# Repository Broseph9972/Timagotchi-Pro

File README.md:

# Timagotchi-Pro
The Timagotchi-Pro is a remake of my magnum opus project, the Timagotchi. for info on that checkout [The original Site](https://timagotchi.dev). this is meant to make it accessible for more than just "School schedules" and moving the price from around $50 without crazy deals to ~~$20.~~ ~~$40~~ ~32[^1] I wanted to make it cooler with a joystick, but i kept the budget as small as possible. kinda wish i didnt tbh.
[^1]:(it will be much cheaper if i ever make multiple, but shipping and using premade devboards and screens make it much more annoying The Timagotchi *(time-a-got-chee)* is a low-cost device that helps with adhd time blindness[^2]
[^2]:You're bad at telling how much time has passed
with a progress bar and other features shown to help people with time blindness at a quick glance with many other useful features.
---

<p align="center">
  
  &nbsp;
  
</p>

# Assembly

To assemble it it simply Solder the buttons, capacitors, screen connector, xiao, speaker, and JST for battery on, then use the FPC cable from the screen, bend it in a "Z" so it fits in the connectors the right way and also plug in the battery it should automatically charge via usb-c. once the pcb is done, There are 2 parts to the cad, a top and bottom half. Insert the pcb, connect the screen afterputting it in the indent on top. put them together with glue, or don't they should still stay together. you may have to seperate the 2 parts in your slicer, but it should work be easily printable.

# Usage
To use it, simply interact with the menu using the buttons like a d-pad. It's very intuitive, im sure you'll understand.

# Why?
I made it becuase i personally have issues telling how much time is left in class, and was really really bored. turned out to be a really really good idea. ive sold these at school to other kids with adhd and actually made profit??? i made the v2 to reduce price and DRASTICALLY improve quality
---
Some upgrades over the earlier version include

- Price reduction
- Speaker
- Nicer buttons
- kinda better case
- No reliance on raspberry pi
- **A Battery**
- Touchscreen

| Quantity | Name                   | Price  | Link                                                                                                                                                                                                                                                                                                                                                                                                                                                                                                                                                                                                                                                            |
| -------- | ---------------------- | ------ | --------------------------------------------------------------------------------------------------------------------------------------------------------------------------------------------------------------------------------------------------------------------------------------------------------------------------------------------------------------------------------------------------------------------------------------------------------------------------------------------------------------------------------------------------------------------------------------------------------------------------------------------------------------- |
| 1        | Conn_01x02_Pin         | $0.11  | https://www.digikey.com/en/products/detail/jst-sales-america-inc/B2B-PH-K-S/926611                                                                                                                                                                                                                                                                                                                                                                                                                                                                                                                                                                              |
| 1        | Speaker                | $4.24  | https://www.digikey.com/en/products/detail/same-sky-formerly-cui-devices/CMS-201438-058S/22602291                                                                                                                                                                                                                                                                                                                                                                                                                                                                                                                                                               |
| 1        | CMS-201438-058S        | $1.60  | https://www.digikey.com/en/products/detail/molex/2005280180/13538830\                                                                                                                                                                                                                                                                                                                                                                                                                                                                                                                                                                                           |
| 1        | XIAO-ESP32-S3-Plus-SMD | $1.86  | Esp32-s3                                                                                                                                                                                                                                                                                                                                                                                                                                                                                                                                                                                                                                                        |
| 1        | MAX98357A              | $6.02  | https://www.aliexpress.us/item/3256807631636428.html?algo_exp_id=60dd1b32-b01c-4ea4-aa7c-080ad8d2e19e-10&pdp_ext_f=%7B%22order%22%3A%2246%22%2C%22eval%22%3A%221%22%2C%22fromPage%22%3A%22search%22%7D&utparam-url=scene%3Asearch%7Cquery_from%3A%7Cx_object_id%3A1005007817951180%7C_p_origin_prod%3A                                                                                                                                                                                                                                                                                                                                                          |
| 1        | PCB                    | $5.22  | JLCPCB                                                                                                                                                                                                                                                                                                                                                                                                                                                                                                                                                                                                                                                          |
| 1        | Battery                | $0.99  | https://www.aliexpress.us/item/3256802733222186.html?spm=a2g0o.productlist.main.2.573662c3rEHzeH&algo_pvid=776a5850-4451-4f10-b9ac-21b38e442e2a&algo_exp_id=776a5850-4451-4f10-b9ac-21b38e442e2a-1&pdp_ext_f=%7B%22order%22%3A%221283%22%2C%22eval%22%3A%221%22%2C%22fromPage%22%3A%22search%22%7D&pdp_npi=6%40dis%21USD%2112.94%210.99%21%21%2112.94%210.99%21%402101d49617782838741088519ed7e7%2112000028368881594%21sea%21US%210%21ABX%211%210%21n_tag%3A-29910%3Bd%3A88f1f0e6%3Bm03_new_user%3A-29895%3BpisId%3A5000000203520967&curPageLogUid=4m6JpZeIsJ89&utparam-url=scene%3Asearch%7Cquery_from%3A%7Cx_object_id%3A1005002919536938%7C_p_origin_prod%3A |
| 1        | Screen                 | $11.99 | https://www.waveshare.com/product/displays/lcd-oled/lcd-oled-3/1.47inch-touch-lcd.htm                                                                                                                                                                                                                                                                                                                                                                                                                                                                                                                                                                           |
|          | Total                  | $32.03 |                                                                                                                                                                                                                                                                                                                                                                                                                                                                                                                                                                                                                                                                 |

This is a project for Hack Club Fallout.

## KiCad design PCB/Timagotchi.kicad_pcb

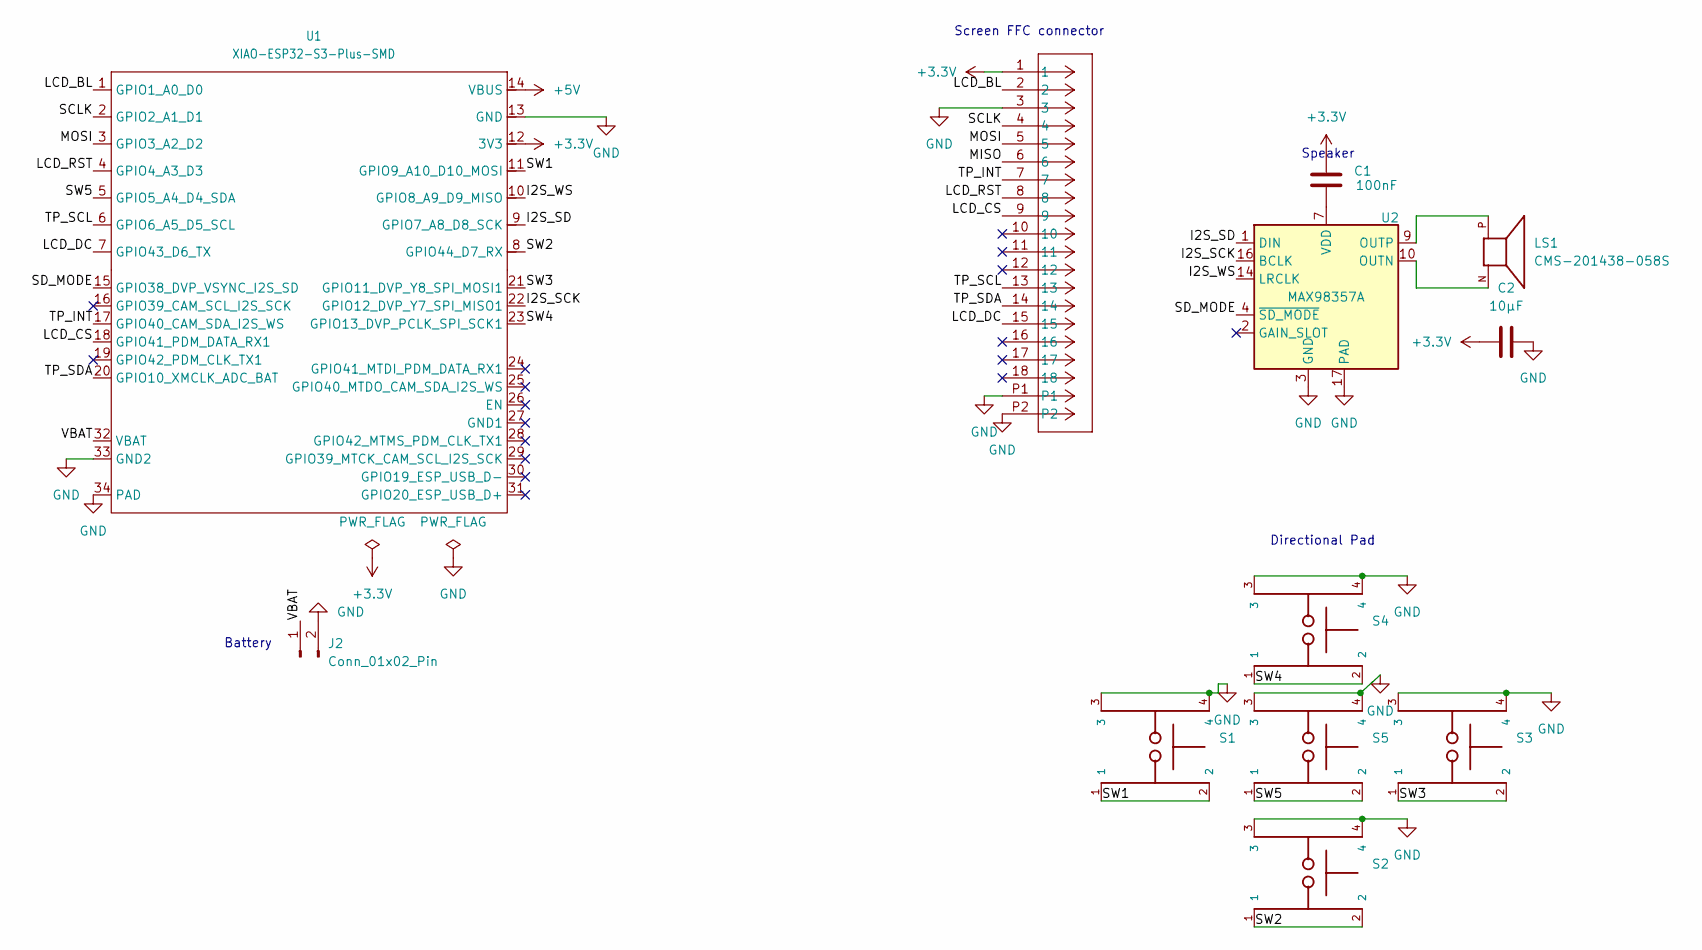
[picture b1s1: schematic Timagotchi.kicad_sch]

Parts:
C1: 100nF; C_0805_2012Metric_Pad1.18x1.45mm_HandSolder
C2: 10µF; C_0805_2012Metric_Pad1.18x1.45mm_HandSolder
J2: Conn_01x02_Pin; JST_PH_B2B-PH-K_1x02_P2.00mm_Vertical
LS1: CMS-201438-058S; SPKR_CMS-201438-058S; PARTREV 1.03
S1, S2, S3, S4, S5: TL3342F160QG; SW_TL3342F160QG
ScreenConnector1: 2005280180; CON_2005280180_MOL
U1: XIAO-ESP32-S3-Plus-SMD
U2: MAX98357A; TQFN-16-1EP_3x3mm_P0.5mm_EP1.23x1.23mm

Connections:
+3.3V: C1.1, C2.1, ScreenConnector1.1, U1.12 (3V3)
+5V: U1.14 (VBUS)
/I2S_SCK: U1.22 (GPIO12_DVP_Y7_SPI_MISO1), U2.16 (BCLK)
/I2S_SD: U1.9 (GPIO7_A8_D8_SCK), U2.1 (DIN)
/I2S_WS: U1.10 (GPIO8_A9_D9_MISO), U2.14 (LRCLK)
/LCD_BL: ScreenConnector1.2, U1.1 (GPIO1_A0_D0)
/LCD_CS: ScreenConnector1.9, U1.18 (GPIO41_PDM_DATA_RX1)
/LCD_DC: ScreenConnector1.15, U1.7 (GPIO43_D6_TX)
/LCD_RST: ScreenConnector1.8, U1.4 (GPIO4_A3_D3)
/MISO: ScreenConnector1.6
/MOSI: ScreenConnector1.5, U1.3 (GPIO3_A2_D2)
/SCLK: ScreenConnector1.4, U1.2 (GPIO2_A1_D1)
/SD_MODE: U1.15 (GPIO38_DVP_VSYNC_I2S_SD), U2.4 (~SD_MODE)
/SW1: S1.1, S1.2, U1.11 (GPIO9_A10_D10_MOSI)
/SW2: S2.1, S2.2, U1.8 (GPIO44_D7_RX)
/SW3: S3.1, S3.2, U1.21 (GPIO11_DVP_Y8_SPI_MOSI1)
/SW4: S4.1, S4.2, U1.23 (GPIO13_DVP_PCLK_SPI_SCK1)
/SW5: S5.1, S5.2, U1.5 (GPIO5_A4_D4_SDA)
/TP_INT: ScreenConnector1.7, U1.17 (GPIO40_CAM_SDA_I2S_WS)
/TP_SCL: ScreenConnector1.13, U1.6 (GPIO6_A5_D5_SCL)
/TP_SDA: ScreenConnector1.14, U1.20 (GPIO10_XMCLK_ADC_BAT)
/VBAT: J2.1, U1.32 (VBAT)
GND: C2.2, J2.2, S1.3, S1.4, S2.3, S2.4, S3.3, S3.4, S4.3, S4.4, S5.3, S5.4, ScreenConnector1.3, ScreenConnector1.P1, ScreenConnector1.P2, U1.13 (GND), U1.33 (GND2), U1.34 (PAD), U2.3 (GND), U2.11 (GND), U2.15 (GND), U2.17 (PAD)
unnamed: C1.2, U2.7 (VDD), U2.8 (VDD)
unnamed: LS1.N, U2.10 (OUTN)
unnamed: LS1.P, U2.9 (OUTP)

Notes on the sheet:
Directional Pad
Battery
Speaker
Screen FFC connector

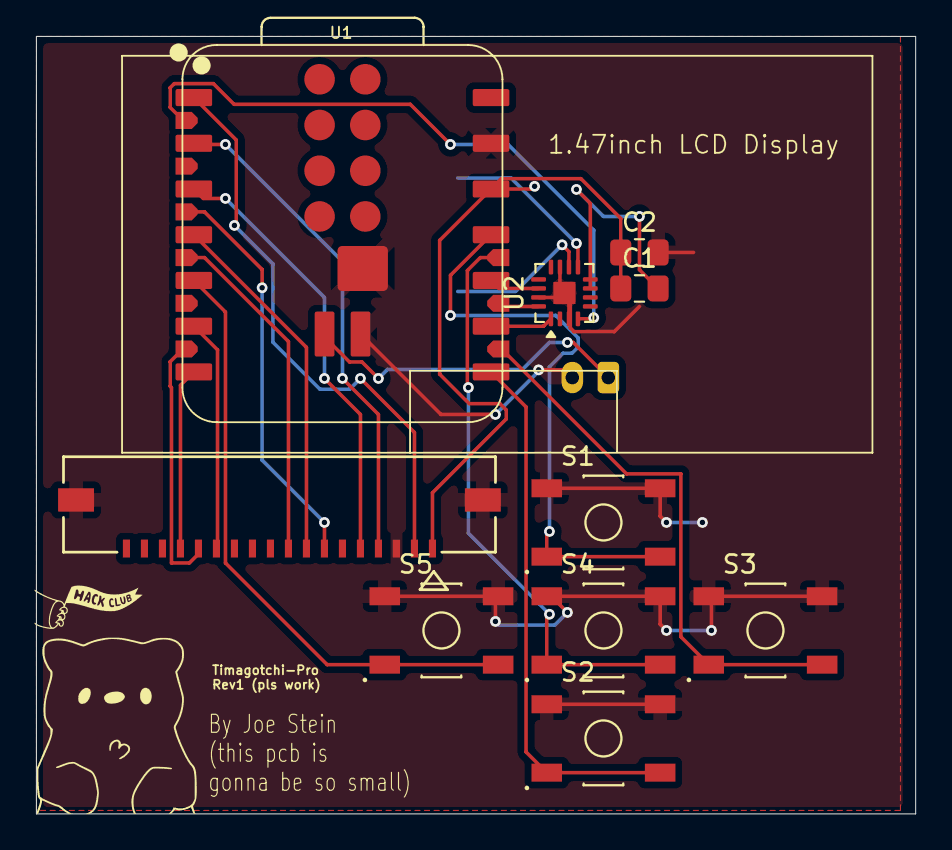
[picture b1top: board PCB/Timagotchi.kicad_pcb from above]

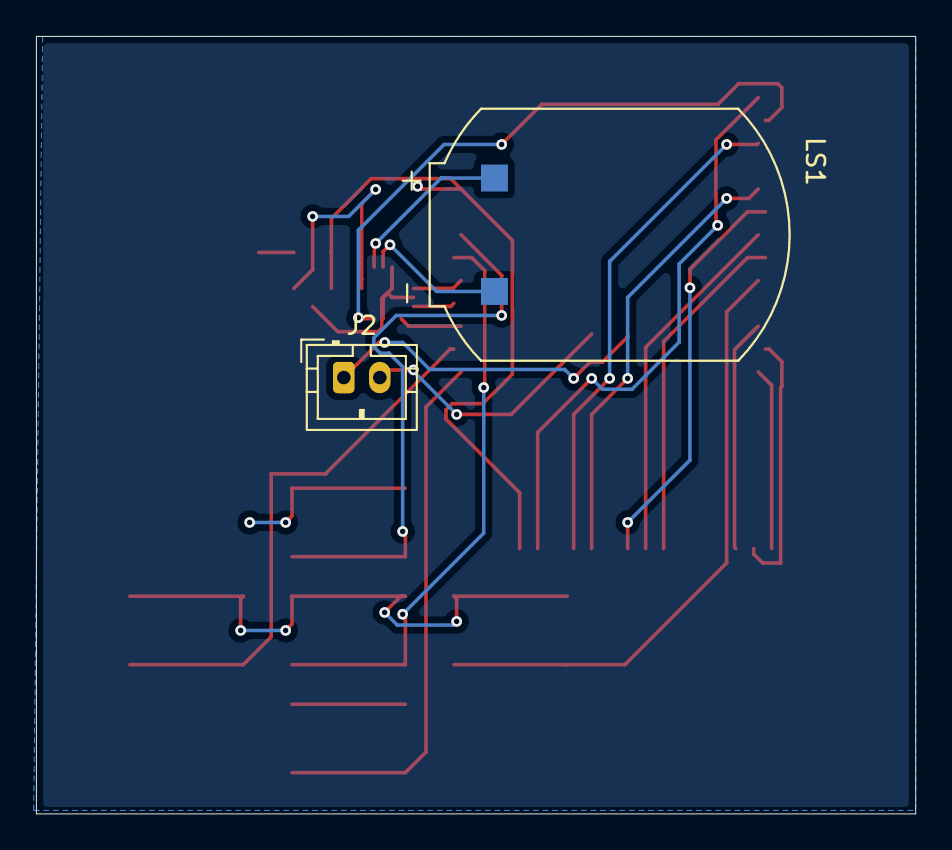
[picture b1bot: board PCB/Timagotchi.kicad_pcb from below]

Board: 2 copper layers, 48.8 x 43.2 mm, 13 parts (2 on the bottom side), 24 nets.

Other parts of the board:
1.47inch LCD Display: 1.47inch LCD Display

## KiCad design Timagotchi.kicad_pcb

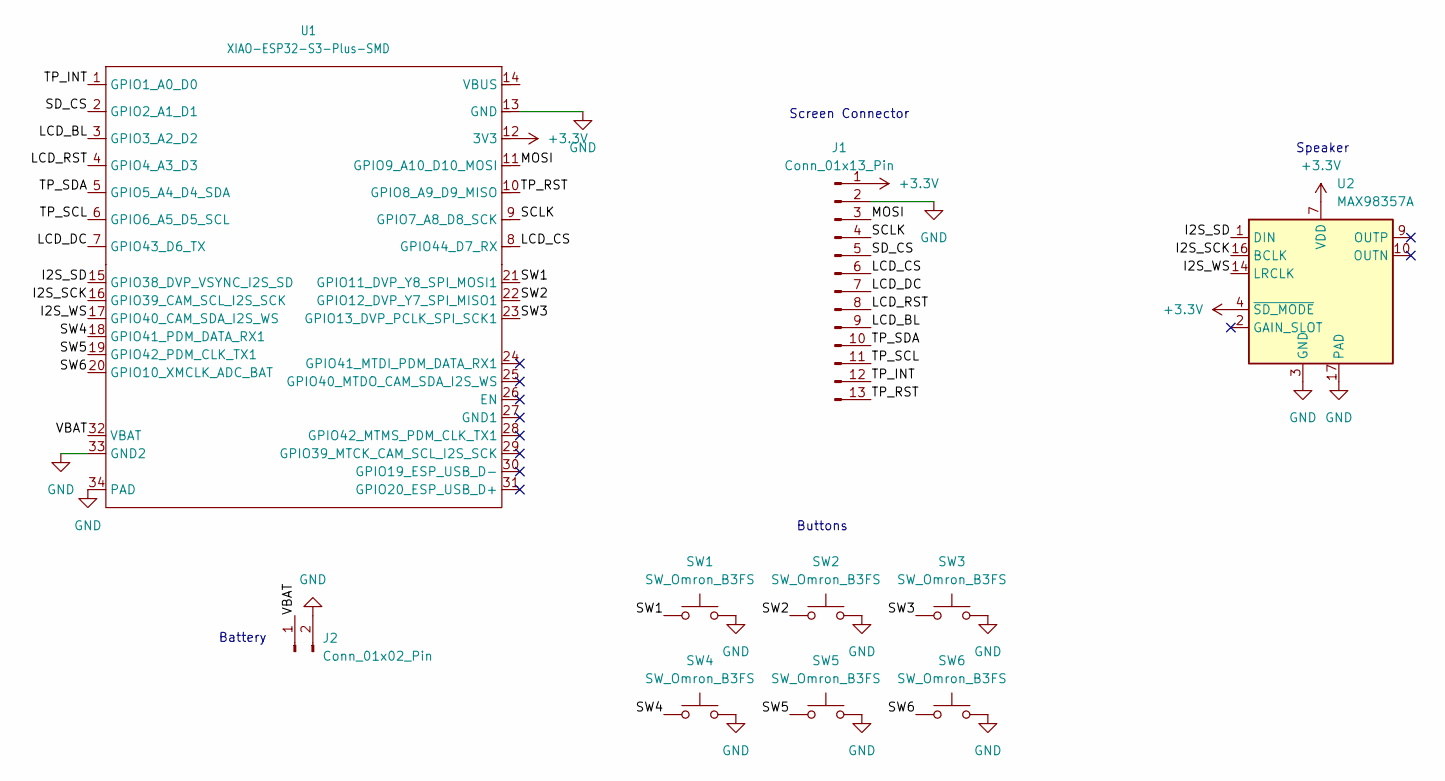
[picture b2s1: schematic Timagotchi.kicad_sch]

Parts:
J1: Conn_01x13_Pin; JST_SH_SM13B-SRSS-TB_1x13-1MP_P1.00mm_Horizontal
J2: Conn_01x02_Pin; JST_PH_B2B-PH-K_1x02_P2.00mm_Vertical
SW1, SW2, SW3, SW4, SW5, SW6: SW_Omron_B3FS; SW_SPST_Omron_B3FS-100xP
U1: XIAO-ESP32-S3-Plus-SMD
U2: MAX98357A; TQFN-16-1EP_3x3mm_P0.5mm_EP1.23x1.23mm

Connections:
+3.3V: J1.1, U1.12 (3V3), U2.4 (~SD_MODE), U2.7 (VDD), U2.8 (VDD)
/I2S_SCK: U1.16 (GPIO39_CAM_SCL_I2S_SCK), U2.16 (BCLK)
/I2S_SD: U1.15 (GPIO38_DVP_VSYNC_I2S_SD), U2.1 (DIN)
/I2S_WS: U1.17 (GPIO40_CAM_SDA_I2S_WS), U2.14 (LRCLK)
/LCD_BL: J1.9, U1.3 (GPIO3_A2_D2)
/LCD_CS: J1.6, U1.8 (GPIO44_D7_RX)
/LCD_DC: J1.7, U1.7 (GPIO43_D6_TX)
/LCD_RST: J1.8, U1.4 (GPIO4_A3_D3)
/MOSI: J1.3, U1.11 (GPIO9_A10_D10_MOSI)
/SCLK: J1.4, U1.9 (GPIO7_A8_D8_SCK)
/SD_CS: J1.5, U1.2 (GPIO2_A1_D1)
/SW1: SW1.1, U1.21 (GPIO11_DVP_Y8_SPI_MOSI1)
/SW2: SW2.1, U1.22 (GPIO12_DVP_Y7_SPI_MISO1)
/SW3: SW3.1, U1.23 (GPIO13_DVP_PCLK_SPI_SCK1)
/SW4: SW4.1, U1.18 (GPIO41_PDM_DATA_RX1)
/SW5: SW5.1, U1.19 (GPIO42_PDM_CLK_TX1)
/SW6: SW6.1, U1.20 (GPIO10_XMCLK_ADC_BAT)
/TP_INT: J1.12, U1.1 (GPIO1_A0_D0)
/TP_RST: J1.13, U1.10 (GPIO8_A9_D9_MISO)
/TP_SCL: J1.11, U1.6 (GPIO6_A5_D5_SCL)
/TP_SDA: J1.10, U1.5 (GPIO5_A4_D4_SDA)
/VBAT: J2.1, U1.32 (VBAT)
GND: J1.2, J2.2, SW1.2, SW2.2, SW3.2, SW4.2, SW5.2, SW6.2, U1.13 (GND), U1.33 (GND2), U1.34 (PAD), U2.3 (GND), U2.11 (GND), U2.15 (GND), U2.17 (PAD)

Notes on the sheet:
Buttons
Battery
Speaker
Screen Connector

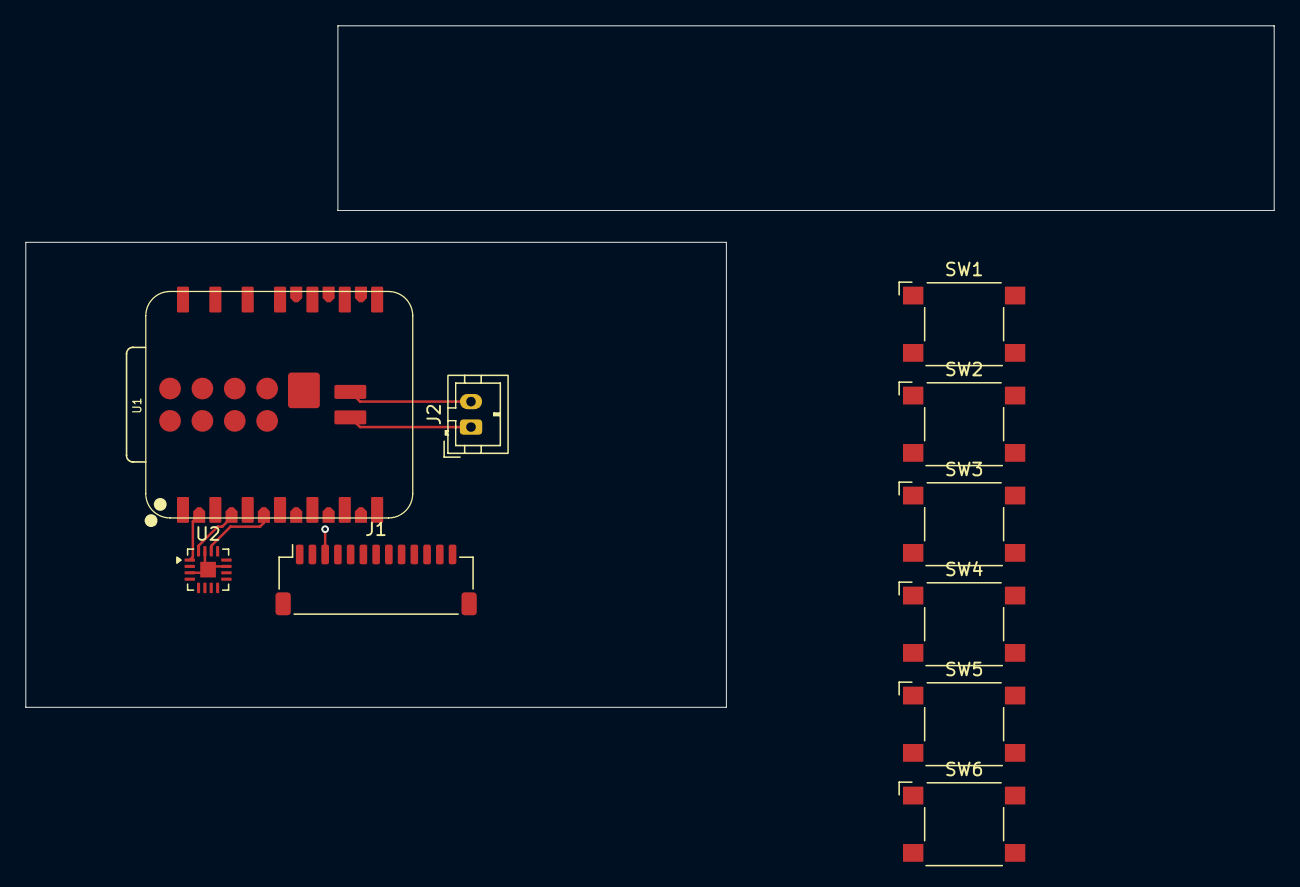
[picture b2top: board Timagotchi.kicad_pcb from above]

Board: 2 copper layers, 98.0 x 53.5 mm, 10 parts (0 on the bottom side), 23 nets.

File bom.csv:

Designator,Footprint,Quantity,Designation,Price,Link
J1,JOYSTICK-PSP1000,1,Conn_01x04,$0.93,PSP 1000
J2,JST_PH_B2B-PH-K_1x02_P2.00mm_Vertical,1,Conn_01x02_Pin,$0.11,JST
LS1,SPKR_CMS-201438-058S,1,CMS-201438-058S,$4.24,Speaker
ScreenConnector1,CON_2005280180_MOL,1,2005280180,$1.86,FFC Connector
"SW1, SW2, SW3",SW_SPST_Omron_B3FS-100xP,3,SW_Omron_B3FS,$0.99,Switches
U1,XIAO-ESP32-S3-Plus-SMD,1,XIAO-ESP32-S3-Plus-SMD,$6.02,Esp32-s3
U2,TQFN-16-1EP_3x3mm_P0.5mm_EP1.23x1.23mm,1,MAX98357A,$1.51,Amplifier
PCB,,1,,$5.22,
Battery,,1,,$1.70,
3d Printed parts,,3,,$0.20,
Screen,,1,,$11.00,
,,,Total,$36.16,

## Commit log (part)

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2026-04-22 Added kicad gitignore from reddit and empty kicad project.
2026-04-22 stole old timagotchi site for later reference
2026-04-23 some work on pcb
2026-04-23 got battery pins and screen setup :)
2026-04-26 Added switches footprints and libraries
2026-04-27 Done for today
2026-04-27 something
2026-04-29 a bunch of stuff
2026-04-29 deleted old site
2026-04-29 made pcb folder
2026-04-30 pcb joystick
2026-05-01 added back the old gitignore brad deleted
2026-05-01 puhcuhbuh
2026-05-02 optimizations and other stuff.
2026-05-03 put stuff in root dir
2026-05-03 found the backup idk 🗿
2026-05-04 added a testfile from wiringpi for python
2026-05-04 Pcb changes, mostly files and 3d models.
2026-05-05 puh cuh buh 2
2026-05-06 wiring and new speaker
    added CMS-201438-058S
    speaker and new gpio wiring
2026-05-06 deleted wiringpi
2026-05-07 PCB wiringgg
2026-05-07 moved the battery connector to the back
2026-05-08 pcb stuff
2026-05-08 Added The BOM
2026-05-08 Rename Timagotchi - Timagotchi.csv to BOM
2026-05-08 Rename BOM to bom.csv
2026-05-08 links to bom
2026-05-11 added the step file
    i think this a dupe but who cares
2026-05-11 new pcb bc the screen wont fit :( but its fixed.
2026-05-12 some change i dunno what
2026-05-13 PCB UHH delete later maybe
2026-05-17 lots of stuff
2026-05-17 wrl file for blender later and a new step file
2026-05-17 Power flags and a nc symbol
2026-05-19 Some stuff
2026-05-19 Stuffs
2026-06-04 add fusion 360 case files
2026-06-04 cad folder
2026-06-13 New pic
2026-06-13 Added the zine
2026-06-17 New zine
2026-06-17 cad cad cad cad cad cad
2026-06-17 Center images in README for improved layout
2026-06-21 Readme stuff
